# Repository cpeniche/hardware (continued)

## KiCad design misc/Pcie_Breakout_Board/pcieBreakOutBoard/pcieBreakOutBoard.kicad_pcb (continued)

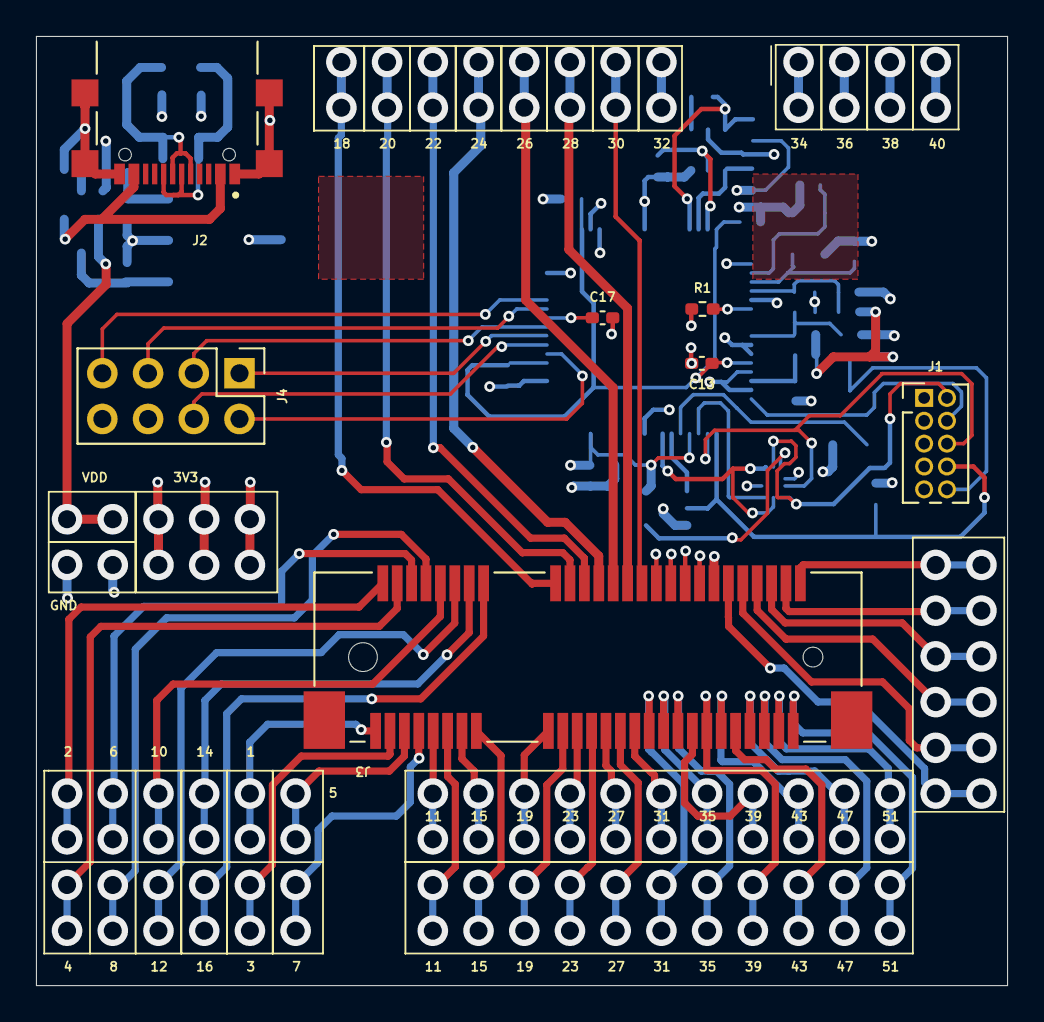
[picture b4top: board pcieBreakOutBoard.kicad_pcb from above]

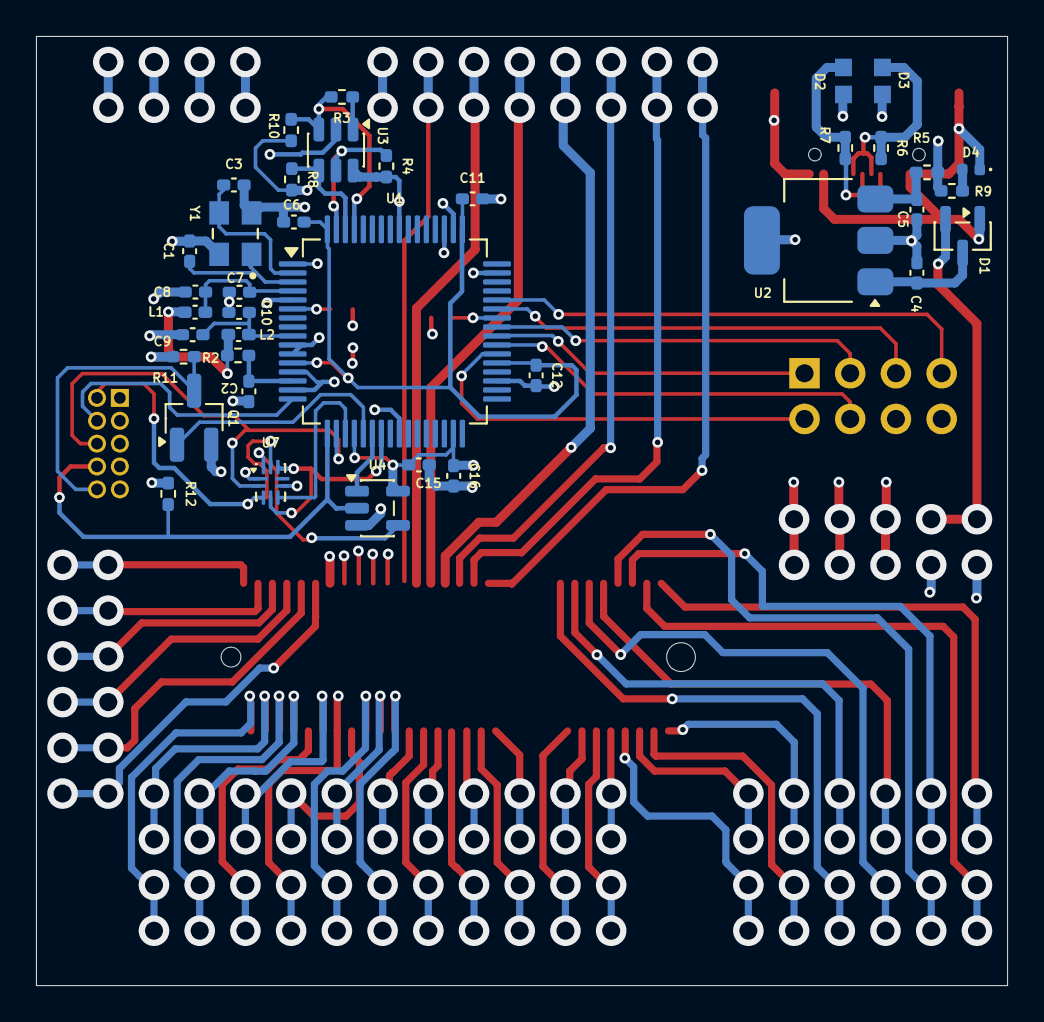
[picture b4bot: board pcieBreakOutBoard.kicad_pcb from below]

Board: 4 copper layers, 54.0 x 52.7 mm, 45 parts (38 on the bottom side), 35 nets.

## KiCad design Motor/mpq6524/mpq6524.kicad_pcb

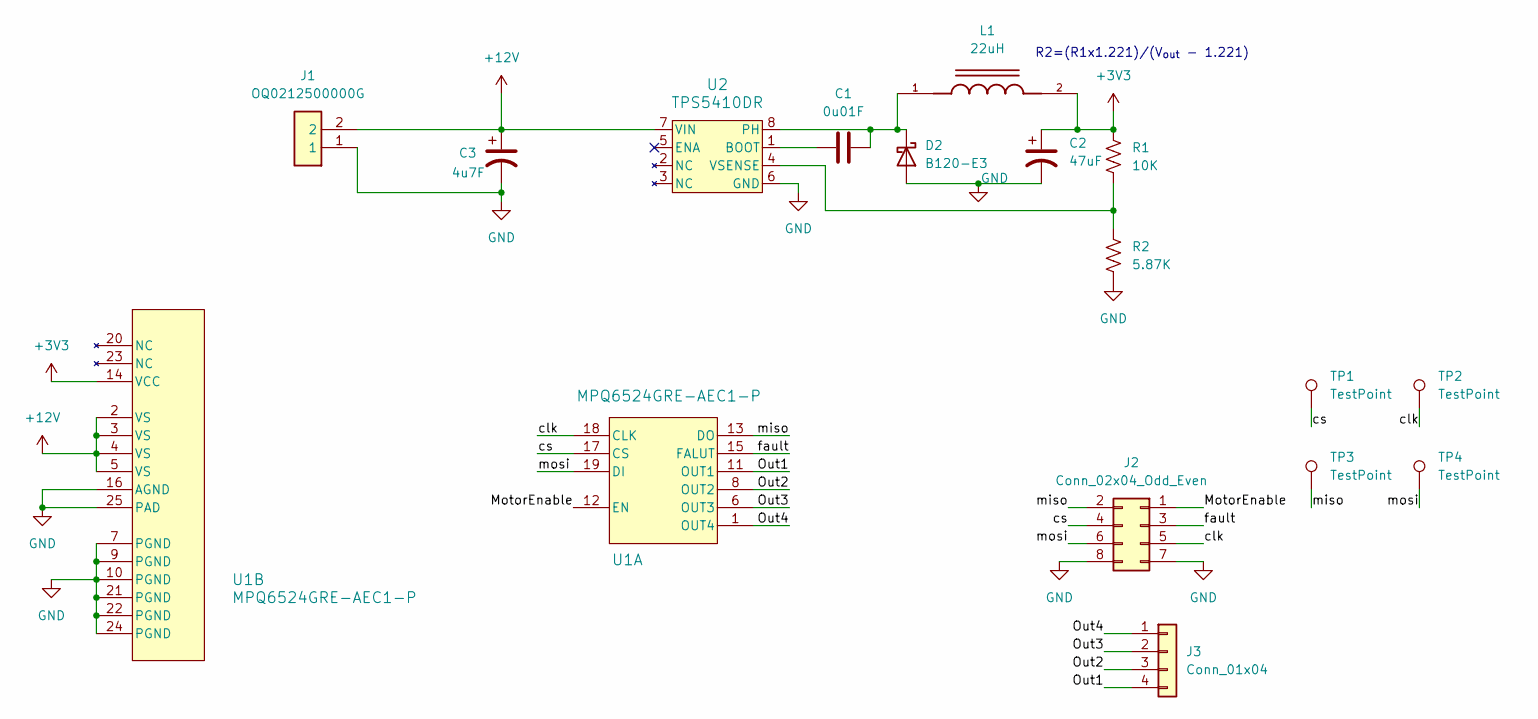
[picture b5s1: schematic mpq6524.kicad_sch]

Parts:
C1: 0u01F; C_0805_2012Metric_Pad1.18x1.45mm_HandSolder
C2: 47uF; CP_EIA-3216-10_Kemet-I_HandSolder
C3: 4u7F; CP_EIA-3528-21_Kemet-B_HandSolder
D2: B120-E3; D_SMA
J1: OQ0212500000G; Mouser Part Number 649-220107-C021A01LF
J2: Conn_02x04_Odd_Even; PinHeader_2x04_P2.54mm_Vertical
J3: Conn_01x04; PinHeader_1x04_P2.54mm_Vertical
L1: 22uH; IND_ASPI-0315FS-220M-T2; PARTREV 11/19/2021
R1: 10K; R_0805_2012Metric_Pad1.20x1.40mm_HandSolder
R2: 5.87K; R_0805_2012Metric_Pad1.20x1.40mm_HandSolder
TP1, TP2, TP3, TP4: TestPoint; TestPoint_Loop_D1.80mm_Drill1.0mm_Beaded
U1: MPQ6524GRE-AEC1-P; QFN-24-1EP_4x4mm_P0.5mm_EP2.5x2.5mm
U2: TPS5410DR; SOIC-8-1EP_3.9x4.9mm_P1.27mm

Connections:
+3V3: C2.1, L1.2, R1.1, U1.14 (VCC)
+12V: C3.1, J1.2, U1.2 (VS), U1.3 (VS), U1.4 (VS), U1.5 (VS), U2.7 (VIN)
/MotorEnable: J2.1, U1.12 (EN)
/Out1: J3.4, U1.11 (OUT1)
/Out2: J3.3, U1.8 (OUT2)
/Out3: J3.2, U1.6 (OUT3)
/Out4: J3.1, U1.1 (OUT4)
/clk: J2.5, TP2.1, U1.18 (CLK)
/cs: J2.4, TP1.1, U1.17 (CS)
/fault: J2.3, U1.15 (FALUT)
/miso: J2.2, TP3.1, U1.13 (DO)
/mosi: J2.6, TP4.1, U1.19 (DI)
GND: C2.2, C3.2, D2.2 (A), J1.1, J2.7, J2.8, R2.2, U1.7 (PGND), U1.9 (PGND), U1.10 (PGND), U1.16 (AGND), U1.21 (PGND), U1.22 (PGND), U1.24 (PGND), U1.25 (PAD), U2.6 (GND)
unnamed: C1.2, D2.1 (K), L1.1, U2.8 (PH)
unnamed: C1.1, U2.1 (BOOT)
unnamed: R1.2, R2.1, U2.4 (VSENSE)

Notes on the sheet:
R2=(R1x1.221)/(V_{out} - 1.221)

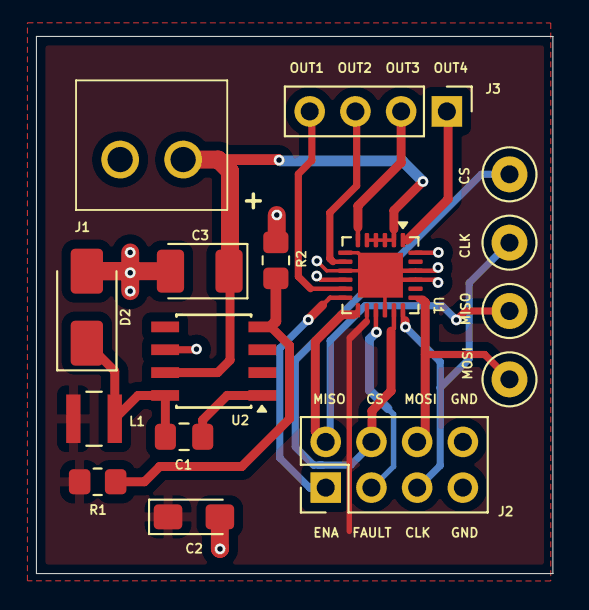
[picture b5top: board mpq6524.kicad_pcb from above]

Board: 2 copper layers, 28.7 x 29.8 mm, 16 parts (0 on the bottom side), 16 nets.

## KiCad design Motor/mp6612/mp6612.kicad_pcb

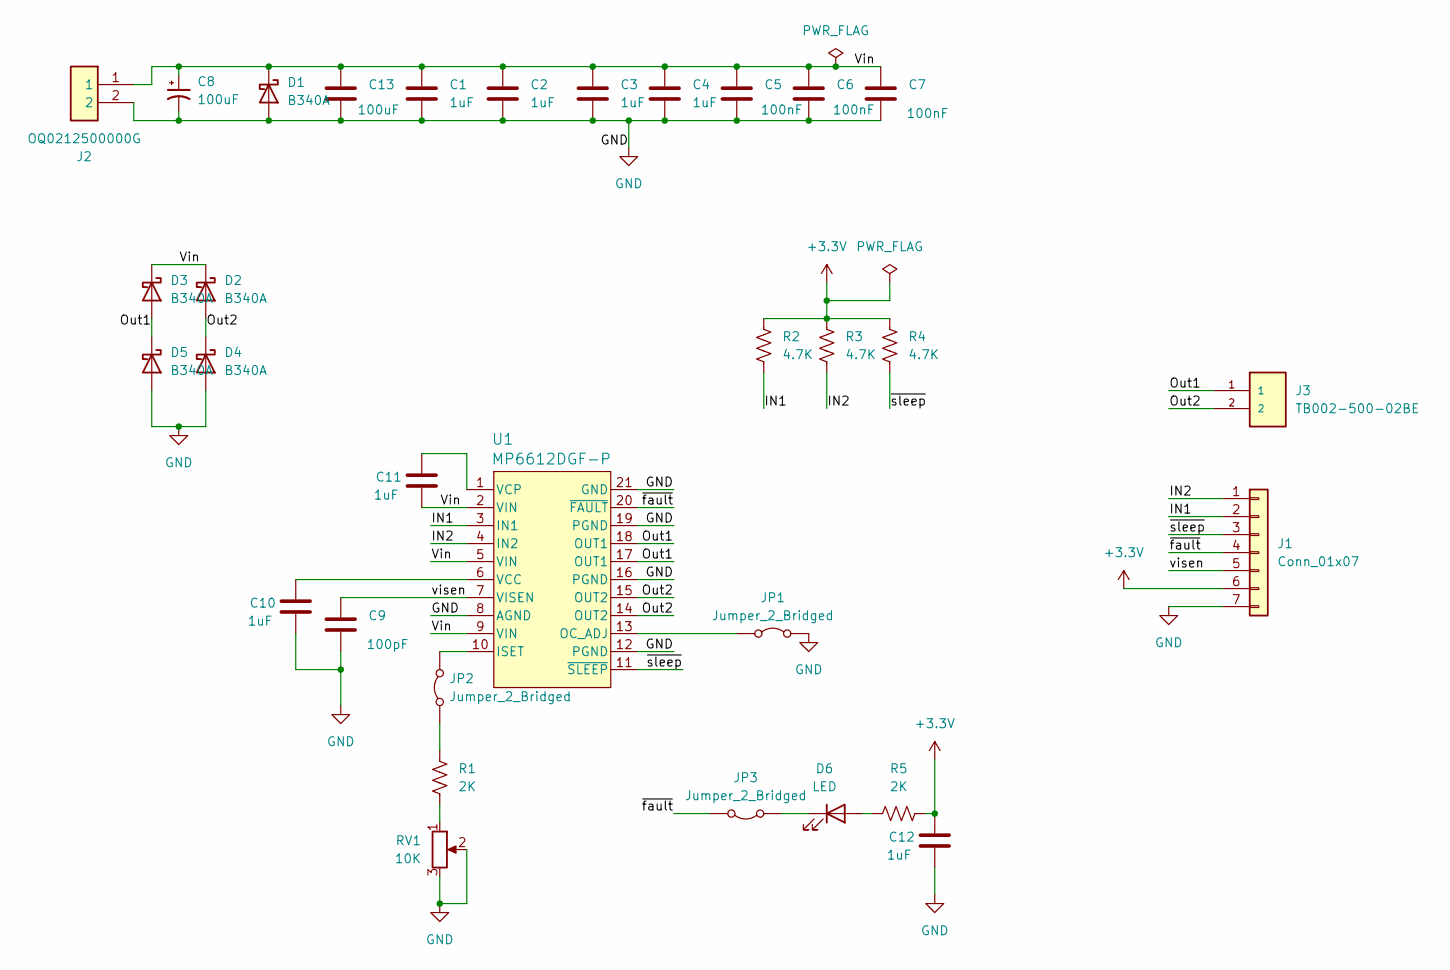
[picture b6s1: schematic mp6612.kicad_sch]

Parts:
C1, C2, C3, C4, C10, C11, C12: 1uF; C_0805_2012Metric_Pad1.18x1.45mm_HandSolder
C5, C6, C7: 100nF; C_0805_2012Metric_Pad1.18x1.45mm_HandSolder
C8: 100uF; CP_EIA-3216-18_Kemet-A_HandSolder
C9: 100pF; C_0805_2012Metric_Pad1.18x1.45mm_HandSolder
C13: 100uF; C_0805_2012Metric_Pad1.18x1.45mm_HandSolder
D1, D2, D3, D4, D5: B340A; D_SMA
D6: LED; LED_0402_1005Metric_Pad0.77x0.64mm_HandSolder
J1: Conn_01x07; PinHeader_1x07_P2.54mm_Vertical
J2: OQ0212500000G; Mouser Part Number 649-220107-C021A01LF
J3: TB002-500-02BE; CUI_TB002-500-02BE
JP1, JP2, JP3: Jumper_2_Bridged; TestPoint_2Pads_Pitch2.54mm_Drill0.8mm
R1, R5: 2K; R_0805_2012Metric_Pad1.20x1.40mm_HandSolder
R2, R3, R4: 4.7K; R_0805_2012Metric_Pad1.20x1.40mm_HandSolder
RV1: 10K; Potentiometer_Runtron_RM-065_Vertical
U1: MP6612DGF-P; TSSOP-20EP_MP6612D_MNP

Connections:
+3.3V: C12.1, J1.6, R2.2, R3.2, R4.2, R5.1
/IN1: J1.2, R2.1, U1.3 (IN1)
/IN2: J1.1, R3.1, U1.4 (IN2)
/Out1: D3.2 (A), D5.1 (K), J3.1, U1.17 (OUT1), U1.18 (OUT1)
/Out2: D2.2 (A), D4.1 (K), J3.2, U1.14 (OUT2), U1.15 (OUT2)
/Vin: C1.1, C2.1, C3.1, C4.1, C5.1, C6.1, C7.1, C8.1, C11.2, C13.1, D1.1 (K), D2.1 (K), D3.1 (K), J2.1, U1.2 (VIN), U1.5 (VIN), U1.9 (VIN)
/visen: C9.1, J1.5, U1.7 (VISEN)
/~fault: J1.4, JP3.2 (B), U1.20 (~FAULT)
/~sleep: J1.3, R4.1, U1.11 (~SLEEP)
GND: C1.2, C2.2, C3.2, C4.2, C5.2, C6.2, C7.2, C8.2, C9.2, C10.2, C12.2, C13.2, D1.2 (A), D4.2 (A), D5.2 (A), J1.7, J2.2, JP1.2 (B), RV1.2, RV1.3, U1.8 (AGND), U1.12 (PGND), U1.16 (PGND), U1.19 (PGND), U1.21 (GND)
unnamed: D6.2 (A), R5.2
unnamed: D6.1 (K), JP3.1 (A)
unnamed: JP1.1 (A), U1.13 (OC_ADJ)
unnamed: JP2.1 (A), R1.2
unnamed: JP2.2 (B), U1.10 (ISET)
unnamed: R1.1, RV1.1
unnamed: C10.1, U1.6 (VCC)
unnamed: C11.1, U1.1 (VCP)

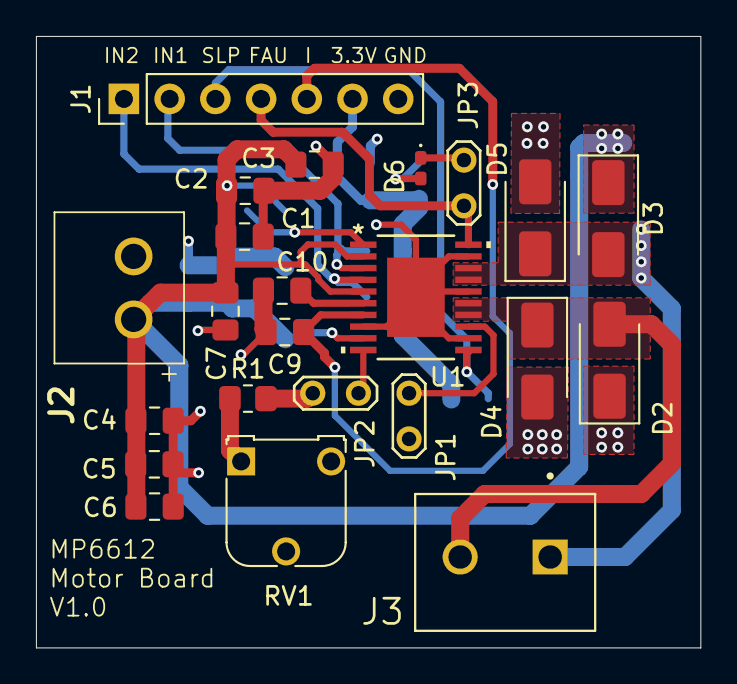
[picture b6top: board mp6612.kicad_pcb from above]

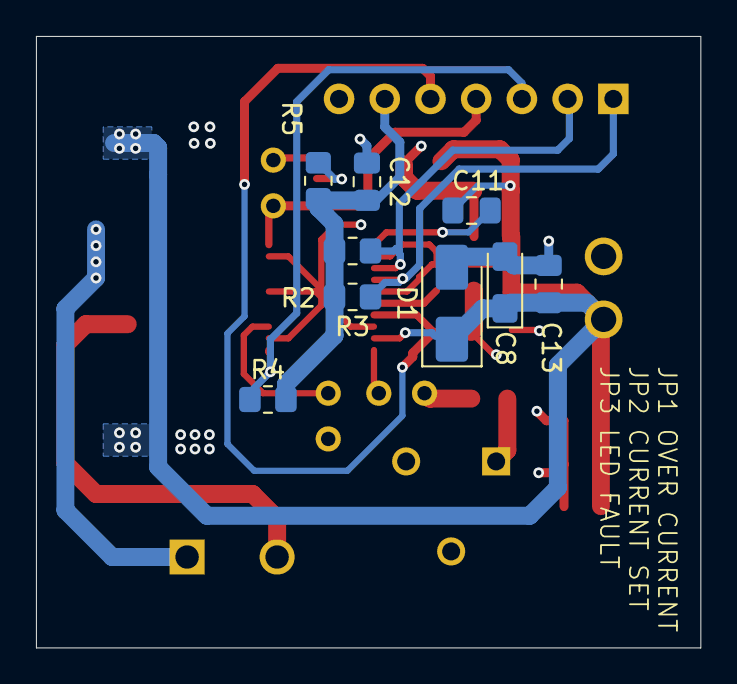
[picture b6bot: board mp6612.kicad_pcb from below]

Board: 4 copper layers, 36.9 x 34.0 mm, 32 parts (9 on the bottom side), 18 nets.

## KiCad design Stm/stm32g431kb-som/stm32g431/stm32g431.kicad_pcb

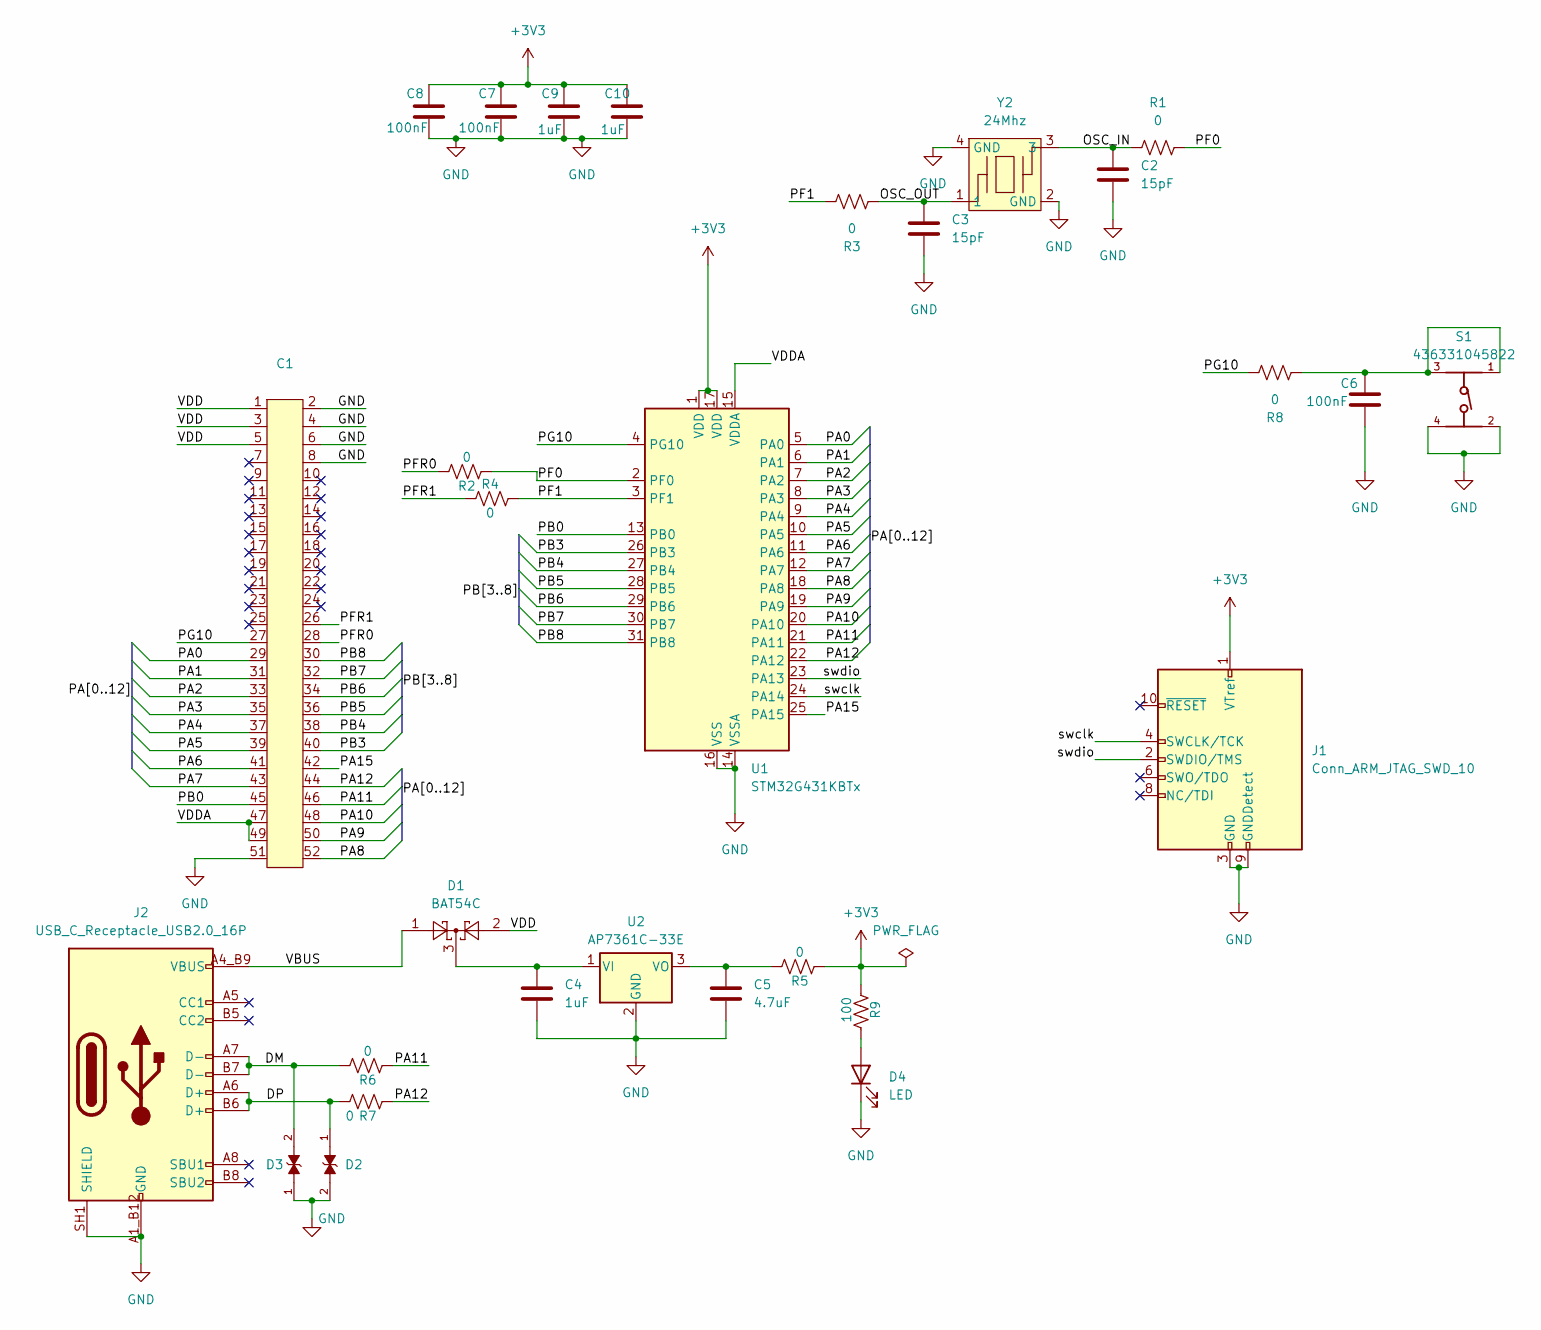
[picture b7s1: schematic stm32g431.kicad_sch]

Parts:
C1: Mini PCI express Half
C2, C3: 15pF; C_0402_1005Metric_Pad0.74x0.62mm_HandSolder
C4, C9, C10: 1uF; C_0402_1005Metric_Pad0.74x0.62mm_HandSolder
C5: 4.7uF; C_0402_1005Metric_Pad0.74x0.62mm_HandSolder
C6, C7, C8: 100nF; C_0402_1005Metric_Pad0.74x0.62mm_HandSolder
D1: BAT54C; SOT-23
D2, D3: PGB1010603NR; DIOC1608X36N
D4: LED; LED_0402_1005Metric
J1: Conn_ARM_JTAG_SWD_10; PinHeader_2x05_P1.27mm_Vertical_SMD
J2: USB_C_Receptacle_USB2.0_16P; AMPHENOL_GSB1C41110SSHR; PARTREV AX1
R1, R2, R3, R4, R5, R6, R7, R8: 0; R_0402_1005Metric_Pad0.72x0.64mm_HandSolder
R9: 100; R_0402_1005Metric_Pad0.72x0.64mm_HandSolder
S1: 436331045822; 4363X10458XX
U1: STM32G431KBTx; LQFP-32_7x7mm_P0.8mm
U2: AP7361C-33E; SOT-223-3_TabPin2
Y2: 24Mhz; jxs11

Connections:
+3V3: C7.1, C8.1, C9.1, C10.1, J1.1 (VTref), R5.2, R9.2, U1.1 (VDD), U1.17 (VDD)
/DM: D3.2, J2.A7 (D-), J2.B7 (D-), R6.1
/DP: D2.1, J2.A6 (D+), J2.B6 (D+), R7.1
/OSC_IN: C2.1, R1.1, Y2.3
/OSC_OUT: C3.1, R3.1, Y2.1
/PA0: C1.29, U1.5 (PA0)
/PA1: C1.31, U1.6 (PA1)
/PA2: C1.33, U1.7 (PA2)
/PA3: C1.35, U1.8 (PA3)
/PA4: C1.37, U1.9 (PA4)
/PA5: C1.39, U1.10 (PA5)
/PA6: C1.41, U1.11 (PA6)
/PA7: C1.43, U1.12 (PA7)
/PA8: C1.52, U1.18 (PA8)
/PA9: C1.50, U1.19 (PA9)
/PA10: C1.48, U1.20 (PA10)
/PA11: C1.46, R6.2, U1.21 (PA11)
/PA12: C1.44, R7.2, U1.22 (PA12)
/PA15: C1.42, U1.25 (PA15)
/PB0: C1.45, U1.13 (PB0)
/PB3: C1.40, U1.26 (PB3)
/PB4: C1.38, U1.27 (PB4)
/PB5: C1.36, U1.28 (PB5)
/PB6: C1.34, U1.29 (PB6)
/PB7: C1.32, U1.30 (PB7)
/PB8: C1.30, U1.31 (PB8)
/PF0: R1.2, R2.2, U1.2 (PF0)
/PF1: R3.2, R4.1, U1.3 (PF1)
/PFR0: C1.28, R2.1
/PFR1: C1.26, R4.2
/PG10: C1.27, R8.2, U1.4 (PG10)
/VBUS: D1.1, J2.A4_B9 (VBUS), J2.B4_A9 (VBUS)
/VDD: C1.1, C1.3, C1.5, D1.2
/VDDA: C1.47, C1.49, U1.15 (VDDA)
/swclk: J1.4 (SWCLK/TCK), U1.24 (PA14)
/swdio: J1.2 (SWDIO/TMS), U1.23 (PA13)
GND: C1.2, C1.4, C1.6, C1.8, C1.51, C2.2, C3.2, C4.2, C5.2, C6.2, C7.2, C8.2, C9.2, C10.2, D2.2, D3.1, D4.1 (K), J1.3 (GND), J1.5 (GND), J1.9 (GNDDetect), J2.A1_B12 (GND), J2.B1_A12 (GND), J2.SH1 (SHIELD), S1.2, S1.4, U1.14 (VSSA), U1.16 (VSS), U1.32 (VSS), U2.2 (GND), Y2.2 (GND), Y2.4 (GND)
unnamed: C6.1, R8.1, S1.1, S1.3
unnamed: D4.2 (A), R9.1
unnamed: C4.1, D1.3, U2.1 (VI)
unnamed: C5.1, R5.1, U2.3 (VO)

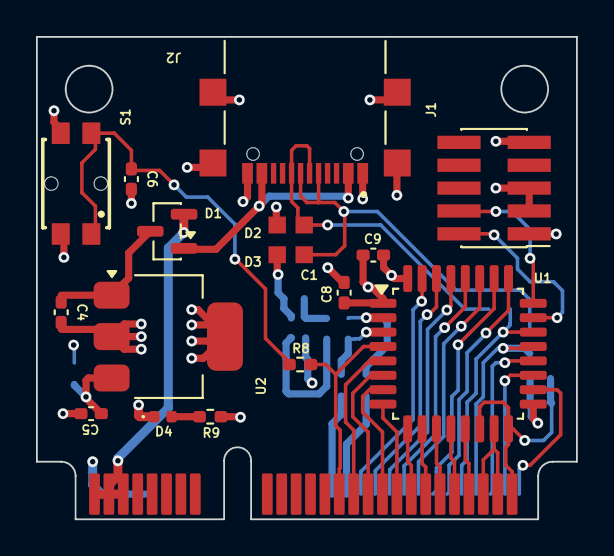
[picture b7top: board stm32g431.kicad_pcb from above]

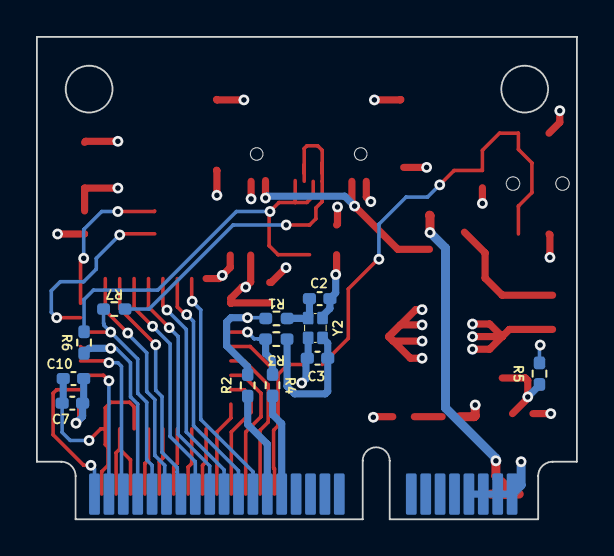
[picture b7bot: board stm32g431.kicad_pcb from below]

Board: 4 copper layers, 30.0 x 26.8 mm, 29 parts (12 on the bottom side), 41 nets.

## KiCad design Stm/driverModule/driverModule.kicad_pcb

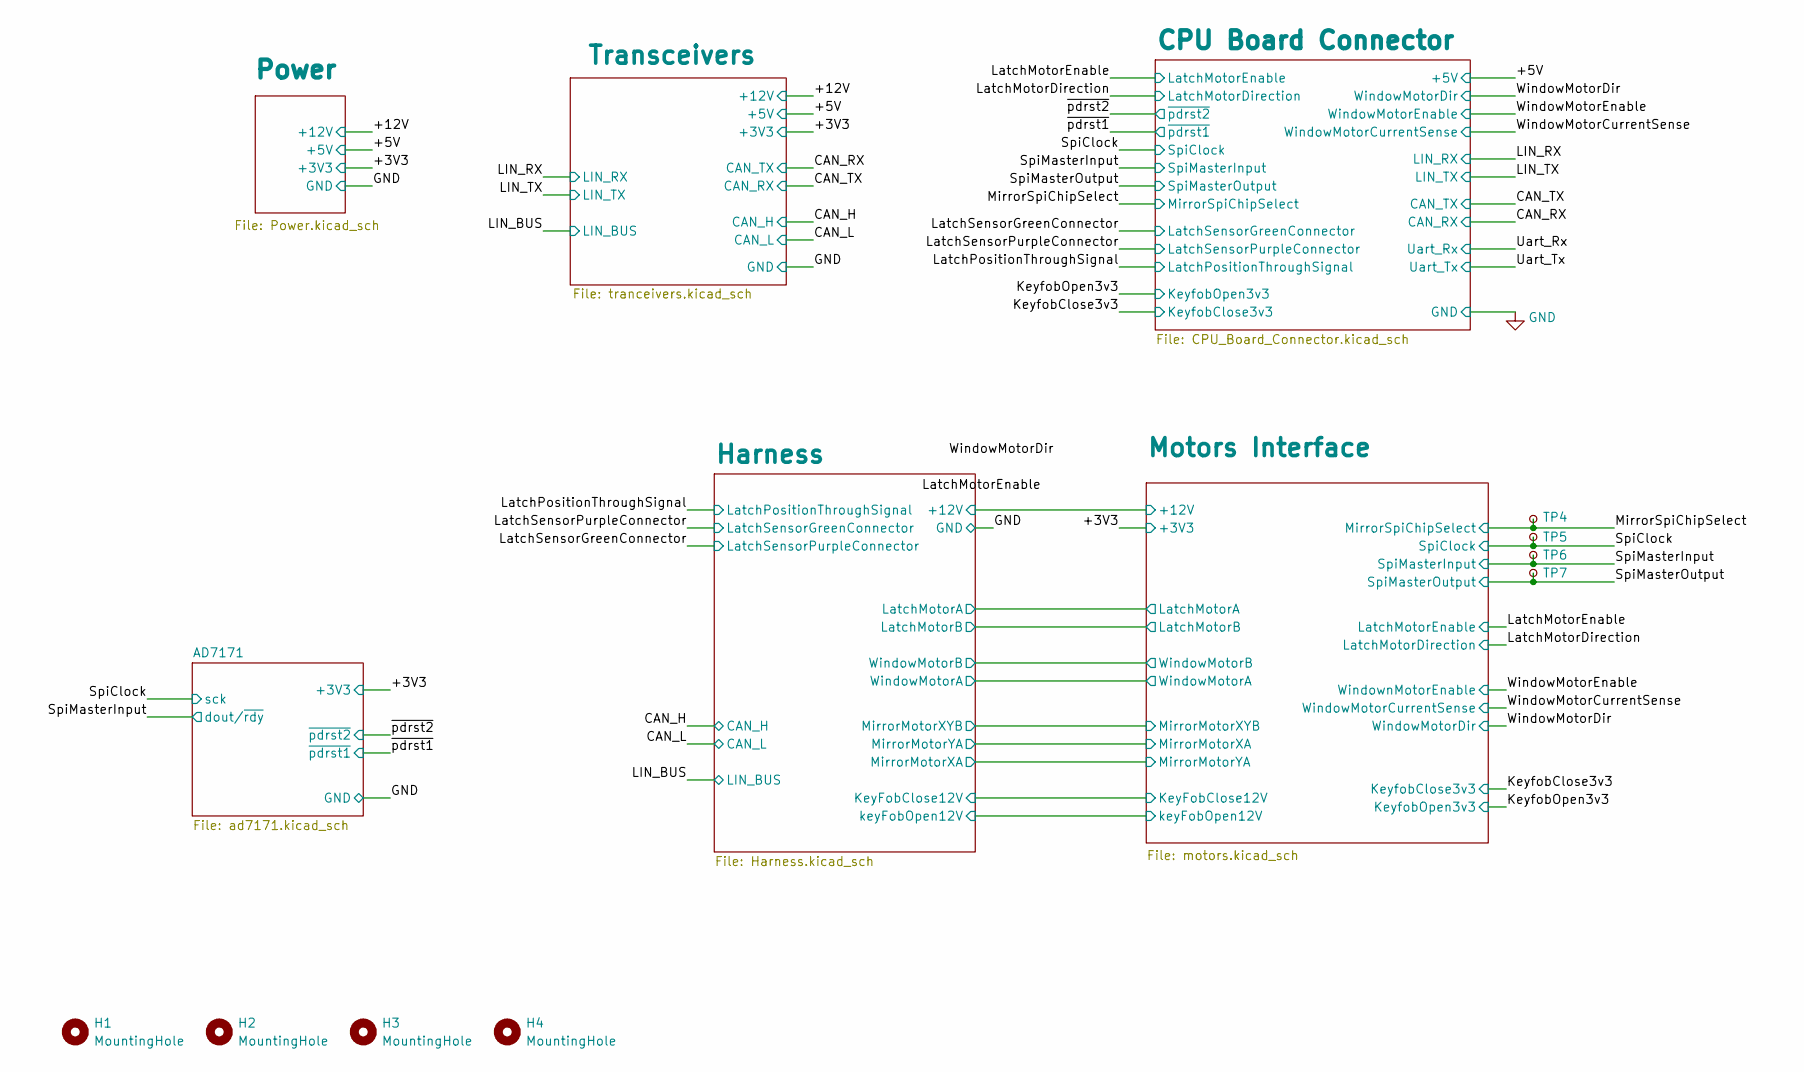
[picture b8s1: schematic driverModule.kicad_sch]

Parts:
H1, H2, H3, H4: MountingHole; MountingHole_2.2mm_M2
TP4, TP5, TP6, TP7: TestPoint_Small; TestPoint_Pad_1.0x1.0mm

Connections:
/MirrorSpiChipSelect: TP4.1; also elsewhere on the board
/SpiClock: TP5.1; also elsewhere on the board
/SpiMasterInput: TP6.1; also elsewhere on the board
/SpiMasterOutput: TP7.1; also elsewhere on the board

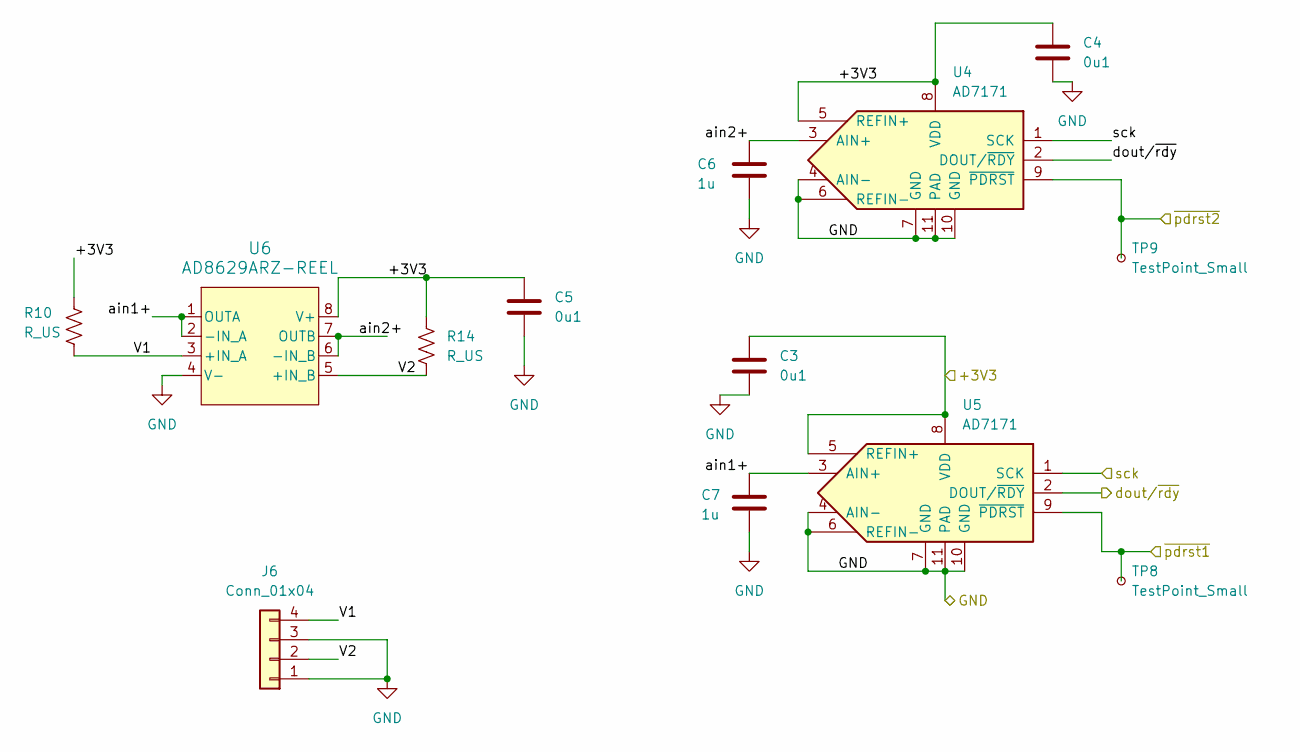
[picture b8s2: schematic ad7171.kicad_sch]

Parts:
C3, C4, C5: 0u1; C_0402_1005Metric_Pad0.74x0.62mm_HandSolder
C6, C7: 1u; C_0402_1005Metric_Pad0.74x0.62mm_HandSolder
J6: Conn_01x04; JST_EH_B4B-EH-A_1x04_P2.50mm_Vertical
R10, R14: R_US; R_0402_1005Metric_Pad0.72x0.64mm_HandSolder
TP8, TP9: TestPoint_Small; TestPoint_Pad_1.0x1.0mm
U4, U5: AD7171; DFN-10-1EP_3x3mm_P0.5mm_EP1.55x2.48mm
U6: AD8629ARZ-REEL; SOIC-8_5.3x5.3mm_P1.27mm

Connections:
+3V3: C3.1, C4.1, C5.1, R10.1, R14.1, U4.5 (REFIN+), U4.8 (VDD), U5.5 (REFIN+), U5.8 (VDD), U6.8 (V+); also elsewhere on the board
/AD7171/V1: J6.4, R10.2, U6.3 (+IN_A)
/AD7171/V2: J6.2, R14.2, U6.5 (+IN_B)
/AD7171/ain1+: C7.1, U5.3 (AIN+), U6.1 (OUTA), U6.2 (-IN_A)
/AD7171/ain2+: C6.1, U4.3 (AIN+), U6.6 (-IN_B), U6.7 (OUTB)
/SpiClock: U4.1 (SCK), U5.1 (SCK); also elsewhere on the board
/SpiMasterInput: U4.2 (DOUT/~RDY), U5.2 (DOUT/~RDY); also elsewhere on the board
/~pdrst1: TP8.1, U5.9 (~PDRST); also elsewhere on the board
/~pdrst2: TP9.1, U4.9 (~PDRST); also elsewhere on the board
GND: C3.2, C4.2, C5.2, C6.2, C7.2, J6.1, J6.3, U4.4 (AIN-), U4.6 (REFIN-), U4.7 (GND), U4.10 (GND), U4.11 (PAD), U5.4 (AIN-), U5.6 (REFIN-), U5.7 (GND), U5.10 (GND), U5.11 (PAD), U6.4 (V-); also elsewhere on the board

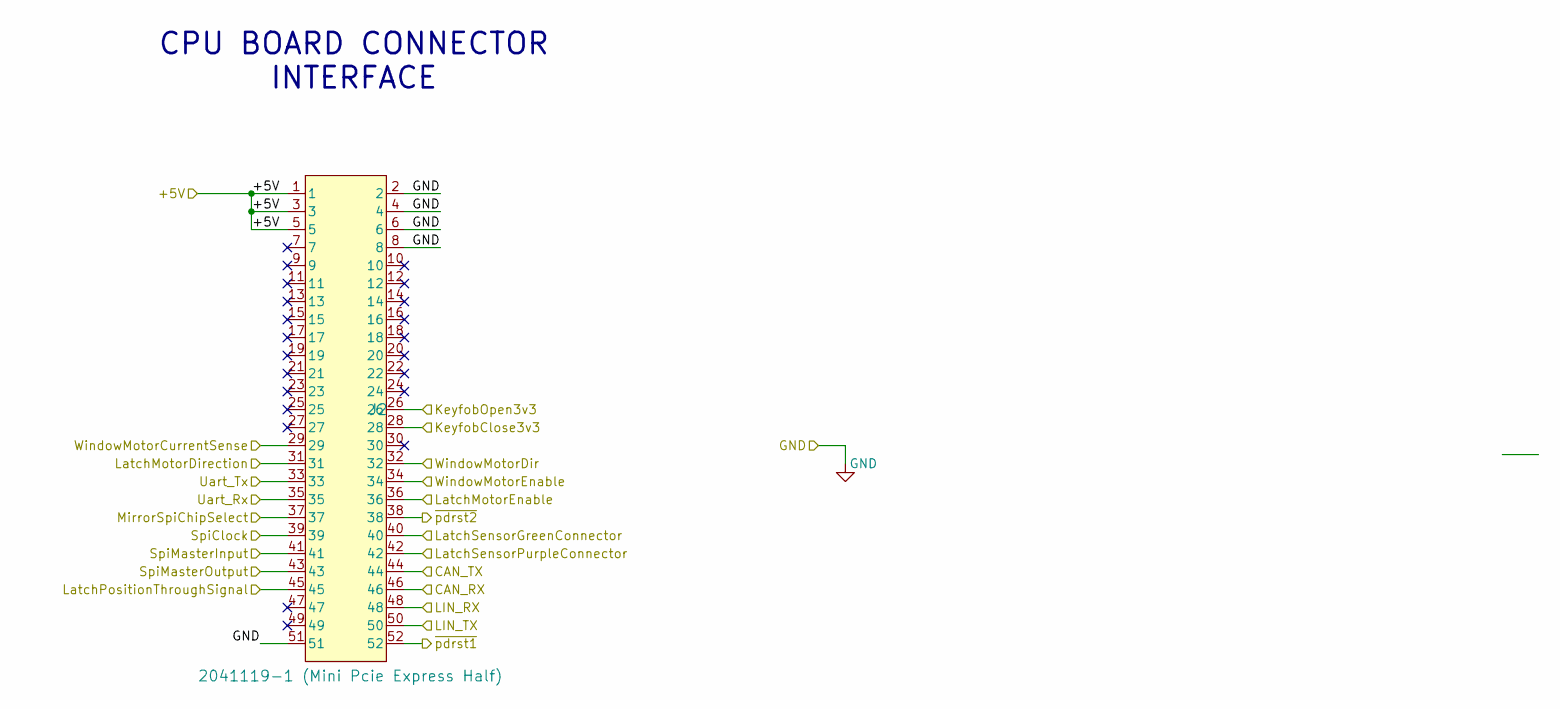
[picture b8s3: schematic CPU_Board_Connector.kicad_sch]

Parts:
J2: 2041119-1 (Mini Pcie Express Half); CONN_2041119-1_TEC

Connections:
+5V: J2.1, J2.3, J2.5; also elsewhere on the board
/CAN_RX: J2.46; also elsewhere on the board
/CAN_TX: J2.44; also elsewhere on the board
/KeyfobClose3v3: J2.28; also elsewhere on the board
/KeyfobOpen3v3: J2.26; also elsewhere on the board
/LIN_RX: J2.48; also elsewhere on the board
/LIN_TX: J2.50; also elsewhere on the board
/LatchMotorDirection: J2.31; also elsewhere on the board
/LatchMotorEnable: J2.36; also elsewhere on the board
/LatchPositionThroughSignal: J2.45; also elsewhere on the board
/LatchSensorGreenConnector: J2.40; also elsewhere on the board
/LatchSensorPurpleConnector: J2.42; also elsewhere on the board
/MirrorSpiChipSelect: J2.37; also elsewhere on the board
/SpiClock: J2.39; also elsewhere on the board
/SpiMasterInput: J2.41; also elsewhere on the board
/SpiMasterOutput: J2.43; also elsewhere on the board
/Uart_Rx: J2.35
/Uart_Tx: J2.33
/WindowMotorCurrentSense: J2.29; also elsewhere on the board
/WindowMotorDir: J2.32; also elsewhere on the board
/WindowMotorEnable: J2.34; also elsewhere on the board
/~pdrst1: J2.52; also elsewhere on the board
/~pdrst2: J2.38; also elsewhere on the board
GND: J2.2, J2.4, J2.6, J2.8, J2.51; also elsewhere on the board

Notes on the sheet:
CPU BOARD CONNECTOR INTERFACE
